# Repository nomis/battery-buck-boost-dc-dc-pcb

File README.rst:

Battery Buck-Boost DC/DC Converter PCB
======================================

Overview
--------

PCB to convert DC/DC from 2-3 AA/AAA batteries to a range of voltages.

Dimensions: 15mm W × 12mm H

Purpose
-------

Fix devices that don't handle the full range of voltages on rechargable
batteries by converting 2-3 AA/AAA batteries to a configurable fixed
output voltage with a low quiescent current.

Usage
-----

This is a KiCad project. Select one of the R1 resistor values to change
the output voltage.

Schematics
----------

.. image:: render/battery-buck-boost-dc-dc-sch.svg
   :alt: Schematic

PCB
---

.. image:: render/battery-buck-boost-dc-dc-pcb.svg
   :alt: PCB

Components
----------

+---------------------+----------+---------------------------------------------------------------+
| Refs                | Quantity | Name                                                          |
+=====================+==========+===============================================================+
| C1                  |     1    | 2.2µF 10V X5R Capacitor, SMD 0805 (Metric 2012)               |
+---------------------+----------+---------------------------------------------------------------+
| C2                  |     1    | 10µF 10V X5R Capacitor, SMD 0805 (Metric 2012)                |
+---------------------+----------+---------------------------------------------------------------+
| D1                  |     1    | Schottky Diode, SMD 0805 (Metric 2012)                        |
+---------------------+----------+---------------------------------------------------------------+
| J1                  |     1    | 1x03 Pin Header, Through Hole (2.54mm)                        |
+---------------------+----------+---------------------------------------------------------------+
| L1                  |     1    | 10µH 500mA 300mΩ Inductor, SMD 0805 (Metric 2012)             |
+---------------------+----------+---------------------------------------------------------------+
| R1 (3.3V)           |     1    | 590kΩ 0.1% 125mW Resistor, SMD 0805 (Metric 2012)             |
+---------------------+----------+---------------------------------------------------------------+
| R1 (4.0V)           |     1    | 442kΩ 0.1% 125mW Resistor, SMD 0805 (Metric 2012)             |
+---------------------+----------+---------------------------------------------------------------+
| R1 (4.5V)           |     1    | 374kΩ 0.1% 125mW Resistor, SMD 0805 (Metric 2012)             |
+---------------------+----------+---------------------------------------------------------------+
| R1 (5.0V)           |     1    | 324kΩ 0.1% 125mW Resistor, SMD 0805 (Metric 2012)             |
+---------------------+----------+---------------------------------------------------------------+
| R2                  |     1    | 1MΩ 0.1% 125mW Resistor, SMD 0805 (Metric 2012)               |
+---------------------+----------+---------------------------------------------------------------+
| U1                  |     1    | LTC3531EDD 200mA Synchronous Buck-Boost DC/DC Converter, SMD  |
+---------------------+----------+---------------------------------------------------------------+

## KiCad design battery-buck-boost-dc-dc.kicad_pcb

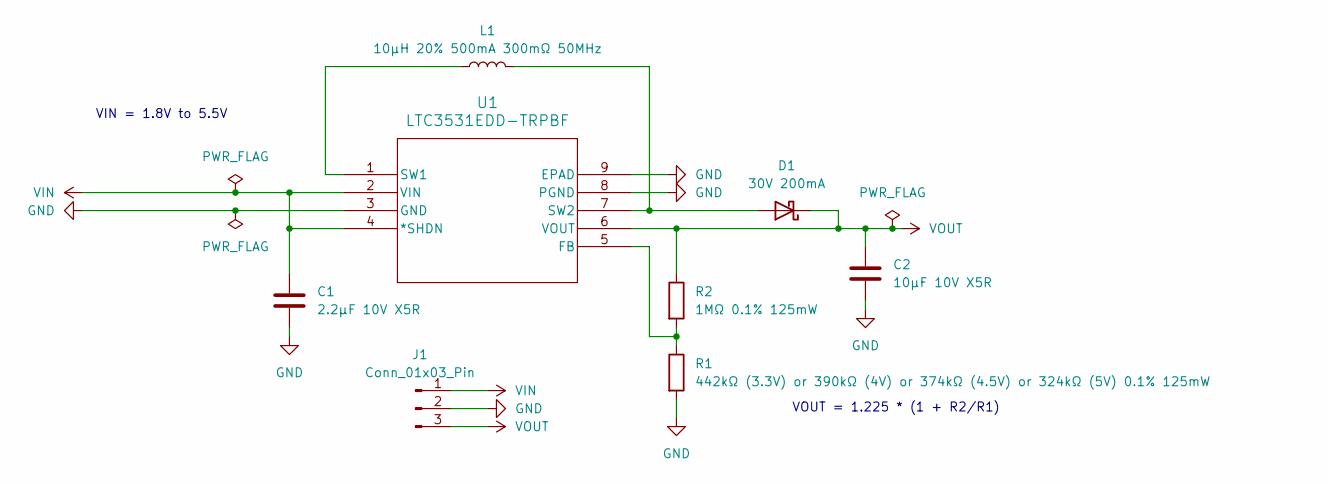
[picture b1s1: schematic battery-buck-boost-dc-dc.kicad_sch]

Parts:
C1: 2.2µF 10V X5R; C_0805_2012Metric
C2: 10µF 10V X5R; C_0805_2012Metric
D1: 30V 200mA; D_0805_2012Metric_Pad1.15x1.40mm_HandSolder
J1: Conn_01x03_Pin; PinHeader_1x03_P2.54mm_Vertical
L1: 10µH 20% 500mA 300mΩ 50MHz; L_0805_2012Metric_Pad1.15x1.40mm_HandSolder
R1: 442kΩ (3.3V) or 390kΩ (4V) or 374kΩ (4.5V) or 324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; R_0805_2012Metric_Pad1.20x1.40mm_HandSolder
R2: 1MΩ 0.1% 125mW; R_0805_2012Metric_Pad1.20x1.40mm_HandSolder
U1: LTC3531EDD-TRPBF; DFN-8_DD_LIT-M

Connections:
GND: C1.2, C2.2, J1.2, R1.2, U1.3 (GND), U1.8 (PGND), U1.9 (EPAD)
unnamed: D1.2 (A), L1.2, U1.7 (SW2)
unnamed: R1.1, R2.2, U1.5 (FB)
unnamed: L1.1, U1.1 (SW1)
VIN: C1.1, J1.1, U1.2 (VIN), U1.4 (*SHDN)
VOUT: C2.1, D1.1 (K), J1.3, R2.1, U1.6 (VOUT)

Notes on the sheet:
VOUT = 1.225 * (1 + R2/R1)
VIN = 1.8V to 5.5V

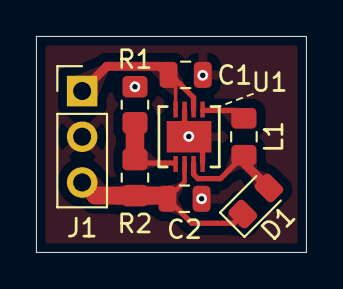
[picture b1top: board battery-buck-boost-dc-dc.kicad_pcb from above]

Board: 2 copper layers, 15.0 x 12.0 mm, 9 parts (1 on the bottom side), 6 nets.

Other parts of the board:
QR: LOGO
